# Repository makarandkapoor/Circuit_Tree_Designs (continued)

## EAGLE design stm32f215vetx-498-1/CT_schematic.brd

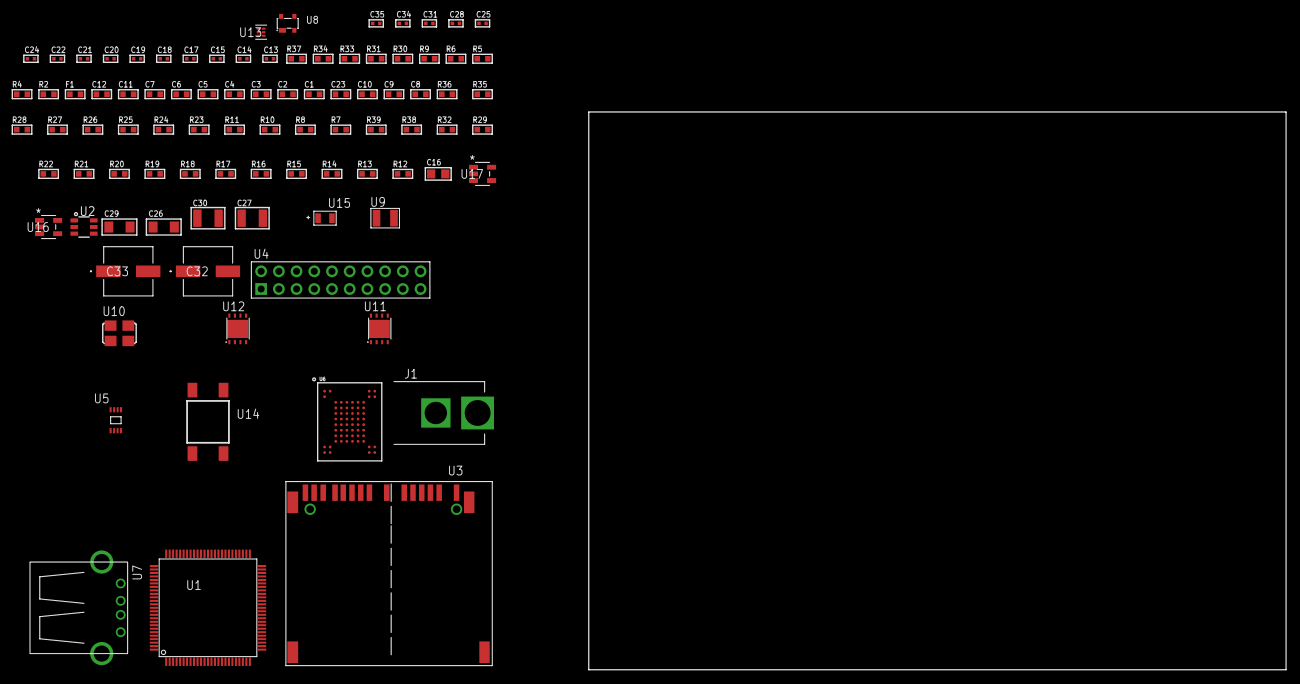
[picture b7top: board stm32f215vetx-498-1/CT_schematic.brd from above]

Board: 2 copper layers, 100.0 x 80.0 mm, 91 parts (0 on the bottom side), 61 nets, no tracks yet.

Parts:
C1, C12: 1e-06; C0603
C2, C3, C4, C5, C6, C7: 1e-07; C0603
C8: 4.7e-06; C0603
C9, C10, C23: 2.2e-06; C0603
C11: 1e-08; C0603
C13, C14: 1e-11; C0402
C15, C17, C19, C20, C21, C22, C31: 1e-07; C0402
C16: 1e-05; C0805
C18, C24, C25, C28, C34, C35: 1e-08; C0402
C26, C29: 1e-05; C1206
C27, C30: 1e-05; C1210
C32, C33: 0.0001; EXV-9H
F1: 240.0; L0603
J1: PJ-037B; PJ-037B_PACKAGE
R2, R31, R34: 1000.0; R0603
R4: 4700.0; R0603
R5, R6: 2200.0; R0603
R7: 47000.0; R0603
R8, R10, R11, R23, R24, R25, R26, R27, R28, R35, R36: 10000.0; R0603
R9: 1270.0; R0603
R12, R13, R14, R15, R16, R17, R18, R19, R20, R21, R22, R29, R32: 100000.0; R0603
R30: 2231.0; R0603
R33: 3900.0; R0603
R37: 9100.0; R0603
R38: 680000.0; R0603
R39: 120000.0; R0603
U1: STM32F215VET6; LQFP100
U2: MAX4995AAUT+T; SOT-23-6
U3: 10100565
U4: TST-110-05-T-D-RA
U5: 24AA04-I/MC; TDFN-8/6MM
U6: mt29f4g08abadah4; VFBGA-63
U7: 61400416021; USB-A-H
U8: prtr5v0u2ax; SOT143B
U9: ABS07-32.768KHZ-7-T
U10: ASFL1-25MHZ-NCS; ASFL1
U11, U12: LP3878SDX-ADJ/NOPB; WSON-8
U13: TPS3895ADRYR; SON-6
U14: 4-1437565-2; SW_4-1437565-2
U15: Q65110A2395; LGM67K-G1J2-24-Z
U16, U17: nc7sz125m5x; NC7SZ125M5X

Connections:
CLK_CRYSTAL_U1_8: C13.1, U1.8, U9.1
CLK_CRYSTAL_U1_9: C14.1, U1.9, U9.2
CLK_U1_12: U1.12, U10.3
GND: C1.2, C2.2, C3.2, C4.2, C5.2, C6.2, C7.2, C8.2, C9.2, C10.2, C11.2, C12.2, C13.2, C14.2, C15.2, C16.2, C17.2, C18.2, C19.2, C20.2, C21.2, C22.2, C23.2, C24.2, C25.2, C26.2, C27.2, C28.2, C29.2, C30.2, C31.2, C32.2, C33.2, C34.2, C35.2, J1.2, R2.2, R7.2, R8.2, R9.2, R11.2, R31.2, R34.2, R37.2, R39.2, U1.10, U1.20, U1.27, U1.74, U2.2, U3.6, U3.10, U3.12, U3.16, U3.17, U3.20, U3.21, U4.4, U4.6, U4.8, U4.10, U4.12, U4.14, U4.16, U4.18, U4.20, U5.4, U5.7, U6.C5, U6.F7, U6.K3, U6.K8, U7.4, U7.5, U7.6, U8.1, U10.2, U11.3, U11.PAD, U12.3, U12.PAD, U13.2, U15.C, U16.2, U16.3, U17.1, U17.3
NET_U1_14: R4.1, U1.14, U17.4
NET_U1_22: C11.1, C12.1, F1.1, U1.21, U1.22
NET_U1_49: C9.1, U1.49
NET_U1_69: R9.1, U1.69
NET_U1_73: C10.1, U1.73
NET_U1_92: R5.1, U1.92, U5.6
NET_U1_93: R6.1, U1.93, U5.5
NET_U1_94: R8.1, U1.94
NET_U1_98: U14.3, U14.4
NET_U2_3: R7.1, U2.3
NET_U3_1: R14.1, U3.1
NET_U3_2: R13.1, U3.2
NET_U3_18: U3.18, U3.19
NET_U6_C3: R28.1, U6.C3
NET_U11_1: C25.1, U11.1
NET_U11_6: R30.2, R31.1, U11.6
NET_U11_8: R29.1, U11.8
NET_U12_1: C28.1, U12.1
NET_U12_6: R33.2, R34.1, U12.6
NET_U12_8: R32.1, U12.8
NET_U13_1: R36.1, R37.1, U13.1
NET_U13_3: R38.2, R39.1, U13.3
NET_U13_4: R35.1, U13.4, U16.4, U17.2
NET_U14_1: R2.1, U14.1, U14.2
PROC_FSMC_D0: U1.61, U6.H4
PROC_FSMC_D1: U1.62, U6.J4
PROC_FSMC_D2: U1.81, U6.K4
PROC_FSMC_D3: U1.82, U6.K5
PROC_FSMC_D4: U1.38, U6.K6
PROC_FSMC_D5: U1.39, U6.J7
PROC_FSMC_D6: U1.40, U6.K7
PROC_FSMC_D7: U1.41, U6.J8
PROC_FSMC_NCE2: R25.1, U1.88, U6.C6
PROC_FSMC_NOE: R27.1, U1.85, U6.D4
PROC_FSMC_NWAIT: R24.1, U1.87, U6.C8
PROC_FSMC_NWE: R26.1, U1.86, U6.C7
PROC_GPIO_TO_U1_USB_FAULT: R10.1, U1.2, U2.6
PROC_GPIO_TO_U1_VBUS_EN: R11.1, U1.1, U2.4
PROC_SDIO_CK: R12.1, U1.80, U3.8
PROC_SDIO_D0: R15.1, U1.65, U3.4
PROC_SDIO_D1: R16.1, U1.66, U3.3
PROC_SDIO_D2: R17.1, U1.78, U3.15
PROC_SDIO_D3: R18.1, U1.79, U3.14
PROC_SDIO_D4: R19.1, U1.95, U3.13
PROC_SDIO_D5: R20.1, U1.96, U3.11
PROC_SDIO_D6: R21.1, U1.63, U3.7
PROC_SDIO_D7: R22.1, U1.64, U3.5
PROC_SYS_JTCK_SWCLK: U1.76, U4.9
PROC_SYS_JTDO_SWO: U1.89, U4.13
PROC_SYS_JTMS_SWDIO: U1.72, U4.7
PROC_USB_OTG_FS_DM: U1.70, U7.2, U8.3
PROC_USB_OTG_FS_DP: U1.71, U7.3, U8.2
PROC_USB_OTG_FS_VBUS: U1.68, U2.1, U7.1, U8.4
RST_OUT_U4_SRESET_B: R23.1, U4.15, U16.1
VCC_S1_8V2: C26.1, C29.1, C32.1, C33.1, J1.1, R29.2, R32.2, U11.4, U12.4
VCC_TIER1_3V3: C1.1, C2.1, C3.1, C4.1, C5.1, C6.1, C7.1, C8.1, C15.1, C16.1, C17.1, C18.1, C19.1, C20.1, C21.1, C22.1, C23.1, C24.1, C27.1, C31.1, C34.1, C35.1, F1.2, R4.2, R5.2, R6.2, R10.2, R12.2, R13.2, R14.2, R15.2, R16.2, R17.2, R18.2, R19.2, R20.2, R21.2, R22.2, R23.2, R24.2, R25.2, R26.2, R27.2, R28.2, R30.1, R35.2, R36.2, R38.1, U1.6, U1.11, U1.19, U1.28, U1.50, U1.75, U1.100, U3.9, U4.1, U5.8, U6.D3, U6.G4, U6.H8, U6.J6, U10.4, U11.5, U13.6, U16.5, U17.5
VCC_TIER1_5V0: C30.1, R33.1, U2.5, U12.5

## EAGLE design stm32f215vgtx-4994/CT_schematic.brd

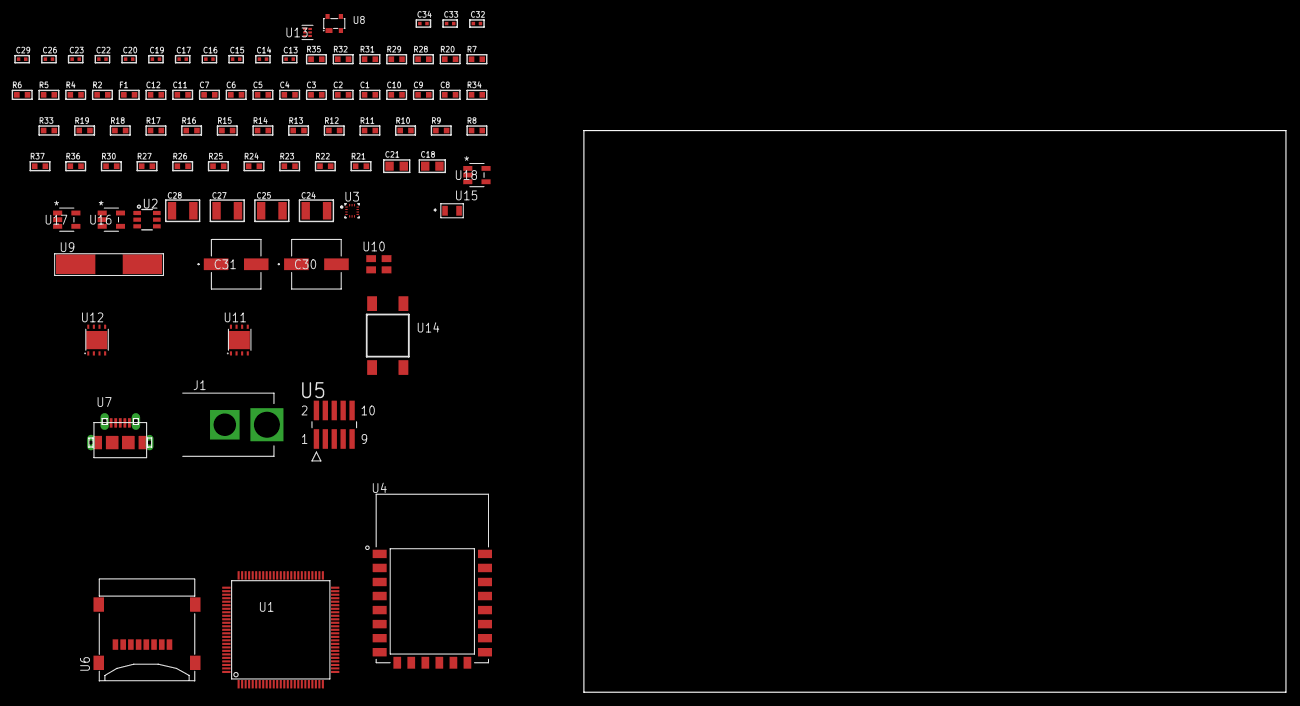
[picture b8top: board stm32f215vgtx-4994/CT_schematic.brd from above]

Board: 2 copper layers, 89 parts (0 on the bottom side), 51 nets, no tracks yet.

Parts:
C1, C12: 1e-06; C0603
C2, C3, C4, C5, C6, C7: 1e-07; C0603
C8: 4.7e-06; C0603
C9, C10: 2.2e-06; C0603
C11: 1e-08; C0603
C13, C14: 1e-11; C0402
C15, C16, C17, C19, C20, C29: 1e-07; C0402
C18, C21: 1e-05; C0805
C22, C23, C26, C32, C33, C34: 1e-08; C0402
C24, C25, C27, C28: 1e-05; C1210
C30, C31: 0.0001; EXV-9H
F1: 240.0; L0603
J1: PJ-037B; PJ-037B_PACKAGE
R2, R29, R32: 1000.0; R0603
R4, R5: 4700.0; R0603
R6, R7: 2200.0; R0603
R8: 47000.0; R0603
R9, R10, R11, R12, R13, R14, R15, R16, R17, R18, R19, R33, R34: 10000.0; R0603
R20: 5.0; R0603
R21, R22, R23, R24, R25, R26, R27, R30: 100000.0; R0603
R28: 2231.0; R0603
R31: 3900.0; R0603
R35: 9100.0; R0603
R36: 680000.0; R0603
R37: 120000.0; R0603
U1: STM32F215VGT6; LQFP100
U2: MAX4995AAUT+T; SOT-23-6
U3: BMC150; LGA14R35P5X6_200X200X100
U4: ESP8266-12E
U5: FTSH-105-01-L-DV-K; SAMTEC_FTSH-105-01-L-DV-K
U6: 0472192001; MOLEX_47219-2001
U7: 47590-0001; MICRO_USB_AB
U8: prtr5v0u2ax; SOT143B
U9: ABLS-25.000MHZ-B2F-T
U10: ASEK-32.768KHz-ECST; ASEK
U11, U12: LP3878SDX-ADJ/NOPB; WSON-8
U13: TPS3895ADRYR; SON-6
U14: 4-1437565-2; SW_4-1437565-2
U15: Q65110A2395; LGM67K-G1J2-24-Z
U16, U17, U18: nc7sz125m5x; NC7SZ125M5X

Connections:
CLK_CRYSTAL_U1_12: C13.1, U1.12, U9.1
CLK_CRYSTAL_U1_13: C14.1, U1.13, U9.2
CLK_U1_8: U1.8, U10.3
GND: C1.2, C2.2, C3.2, C4.2, C5.2, C6.2, C7.2, C8.2, C9.2, C10.2, C11.2, C12.2, C13.2, C14.2, C15.2, C16.2, C17.2, C18.2, C19.2, C20.2, C21.2, C22.2, C23.2, C24.2, C25.2, C26.2, C27.2, C28.2, C29.2, C30.2, C31.2, C32.2, C33.2, C34.2, J1.2, R2.2, R8.2, R9.2, R11.2, R15.2, R19.2, R20.2, R29.2, R32.2, R35.2, R37.2, U1.10, U1.20, U1.27, U1.74, U2.2, U3.1, U3.6, U3.7, U3.9, U4.15, U5.3, U5.5, U6.6, U6.G1, U6.G2, U6.G3, U6.G4, U7.5, U7.6, U7.7, U7.8, U7.9, U8.1, U10.2, U11.3, U11.PAD, U12.3, U12.PAD, U13.2, U15.C, U16.2, U16.3, U17.1, U17.3, U18.1, U18.3
NET_U1_14: R5.1, U1.14, U18.4
NET_U1_22: C11.1, C12.1, F1.1, U1.21, U1.22
NET_U1_49: C9.1, U1.49
NET_U1_73: C10.1, U1.73
NET_U1_92: R6.1, U1.92, U3.11
NET_U1_93: R7.1, U1.93, U3.14
NET_U1_94: R9.1, U1.94
NET_U1_98: U14.3, U14.4
NET_U2_3: R8.1, U2.3
NET_U4_1: R4.1, U4.1, U17.4
NET_U4_3: R13.1, U4.3
NET_U4_18: R14.1, U4.18
NET_U5_9: R20.1, U5.9
NET_U11_1: C23.1, U11.1
NET_U11_6: R28.2, R29.1, U11.6
NET_U11_8: R27.1, U11.8
NET_U12_1: C26.1, U12.1
NET_U12_6: R31.2, R32.1, U12.6
NET_U12_8: R30.1, U12.8
NET_U13_1: R34.1, R35.1, U13.1
NET_U13_3: R36.2, R37.1, U13.3
NET_U13_4: R33.1, U13.4, U16.4, U17.2, U18.2
NET_U14_1: R2.1, U14.1, U14.2
PROC_GPIO_TO_U1_USB_FAULT: R10.1, U1.2, U2.6
PROC_GPIO_TO_U1_VBUS_EN: R11.1, U1.1, U2.4
PROC_SDIO_CK: R22.1, U1.80, U6.5
PROC_SDIO_CMD: R21.1, U1.83, U6.3
PROC_SDIO_D0: R23.1, U1.65, U6.7
PROC_SDIO_D1: R24.1, U1.66, U6.8
PROC_SDIO_D2: R25.1, U1.78, U6.1
PROC_SDIO_D3: R26.1, U1.79, U6.2
PROC_SPI1_MISO: U1.31, U4.6
PROC_SPI1_MOSI: U1.32, U4.7
PROC_SPI1_NSS: R15.1, U1.29, U4.16
PROC_SPI1_SCK: U1.30, U4.5
PROC_SYS_JTCK_SWCLK: R19.1, U1.76, U5.4
PROC_SYS_JTDI: R17.1, U1.77, U5.8
PROC_SYS_JTDO_SWO: U1.89, U5.6
PROC_SYS_JTMS_SWDIO: R18.1, U1.72, U5.2
PROC_USB_OTG_FS_DM: U1.70, U7.2, U8.3
PROC_USB_OTG_FS_DP: U1.71, U7.3, U8.2
PROC_USB_OTG_FS_ID: U1.69, U7.4
PROC_USB_OTG_FS_VBUS: U1.68, U2.1, U7.1, U8.4
RST_OUT_U5_JTAG_RST_B: R16.1, U5.10, U16.1
VCC_S1_15V8: C24.1, C27.1, C30.1, C31.1, J1.1, R27.2, R30.2, U11.4, U12.4
VCC_TIER1_3V3: C1.1, C2.1, C3.1, C4.1, C5.1, C6.1, C7.1, C8.1, C15.1, C16.1, C17.1, C18.1, C19.1, C20.1, C21.1, C22.1, C25.1, C29.1, C32.1, C33.1, C34.1, F1.2, R4.2, R5.2, R6.2, R7.2, R10.2, R12.1, R12.2, R13.2, R14.2, R16.2, R17.2, R18.2, R21.2, R22.2, R23.2, R24.2, R25.2, R26.2, R28.1, R33.2, R34.2, R36.1, U1.6, U1.11, U1.19, U1.28, U1.50, U1.75, U1.100, U3.8, U3.10, U3.12, U3.13, U4.8, U5.1, U6.4, U10.4, U11.5, U13.6, U16.5, U17.5, U18.5
VCC_TIER1_5V0: C28.1, R31.1, U2.5, U12.5
